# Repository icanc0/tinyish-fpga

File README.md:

# tinyish-fpga

The TinyFPGA-BX adapted to USB-C and the CM-121 package.

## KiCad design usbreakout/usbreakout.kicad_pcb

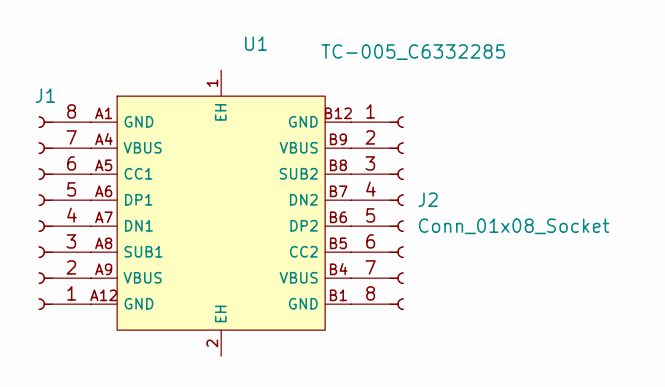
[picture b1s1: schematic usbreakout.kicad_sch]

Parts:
J1, J2: Conn_01x08_Socket; PinSocket_1x08_P2.54mm_Vertical
U1: TC-005_C6332285; USB-C-SMD_TC-005; LCSC C6332285

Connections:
unnamed: J1.1, U1.A12 (GND)
unnamed: J1.2, U1.A9 (VBUS)
unnamed: J1.3, U1.A8 (SUB1)
unnamed: J1.4, U1.A7 (DN1)
unnamed: J1.5, U1.A6 (DP1)
unnamed: J1.6, U1.A5 (CC1)
unnamed: J1.7, U1.A4 (VBUS)
unnamed: J1.8, U1.A1 (GND)
unnamed: J2.1, U1.B12 (GND)
unnamed: J2.2, U1.B9 (VBUS)
unnamed: J2.3, U1.B8 (SUB2)
unnamed: J2.4, U1.B7 (DN2)
unnamed: J2.5, U1.B6 (DP2)
unnamed: J2.6, U1.B5 (CC2)
unnamed: J2.7, U1.B4 (VBUS)
unnamed: J2.8, U1.B1 (GND)

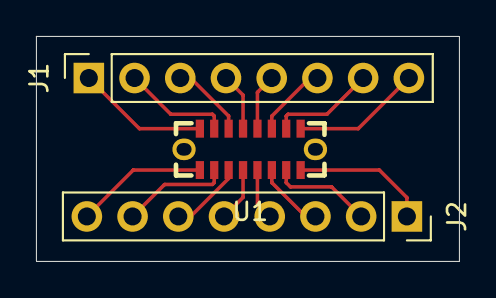
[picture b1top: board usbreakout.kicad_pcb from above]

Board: 2 copper layers, 23.5 x 12.5 mm, 3 parts (0 on the bottom side), 16 nets.

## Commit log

2024-03-03 initial parts
2024-03-03 Add original board
2024-03-03 Remove locks
2024-03-03 updated git ignore
2024-03-03 Move relevant files to root
2024-03-03 added manila ice
2024-03-03 Move tinyfpga components to main schem
2024-03-04 Add usb breakout board
2024-03-04 Add footprints and symbols
2024-03-05 Switch usb, LDOs
2024-03-09 Hook up some data pins to usb-c
2024-03-09 Start connecting the board (reset + usb-c breakouts)
2024-03-09 Replace 16p usb-c with 24p usb-c
2024-03-09 Finish wiring PIO (no DPIO yet) and add Mems and Flash
2024-03-09 Add workflow to generate pdf on push
2024-03-09 Add files to gitignore
2024-03-09 Small adjustments
2024-03-09 Hook up USB 2 d and USB 3 tx+rx
2024-03-09 Update README and add badge
2024-03-10 Swap bank 2 breakout for 2x USB2.0 connectors + IO
